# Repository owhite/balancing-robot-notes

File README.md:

# Balancing Robot Design and Implementation

This repository is a structured set of lab notes and implementation records for developing a two-wheeled self-balancing robot. It documents the workflows from physical modeling and parameter measurement through firmware design, control implementation, and experimental validation.

The focus is on reproducibility and engineering rigor: measured motor parameters, deterministic control-loop behavior, system identification, control design tradeoffs, and verification testing are all captured alongside working code and experiments.

Topics covered include:
- Control design and validation workflows for balancing robots
- Motor parameter measurement (phase resistance, d/q inductance, damping)
- Deterministic embedded firmware structure for real-time control
- Encoder integration and signal integrity checks
- CAN communication and timing behavior
- Failure modes and debugging notes
- Practical test methods and instrumentation results

These notes are intended to make the development and validation process transparent and repeatable, not just to present final code.

## My balancing robot journey, specs and testing

* A subset of steps required to get a robot to stand [[LINK](DOCS/balancing_checklist.md)]
* Common issues that can break balancing in the brain board project [[LINK](DOCS/balancing_failures.md)]
* Firmware design choices that keep the balancing control loop deterministic [[LINK](DOCS/determinism_design.md)]
* Measuring phase resistance, d-axis, and q-axis inductance of a BLDC Motor [[LINK](DOCS/BLDC_inductance_measurement.md)]
* Prompt ChatGPT so it is less of a exhuberant cheerleader and more of a skeptical lab partner: [[LINK](DOCS/chatGPT_tips.md)]
* Development of the robot control board [[LINK](brainboardV1.2/README.md)]

## Not totally coherent discussions:
* [LQR](DOCS/learn_LQR.md). 
* Using the MT6701 [[LINK](DOCS/MT6701.md)] → works great but required some minor modifications to MESC position and [velocity measurement](DOCS/pos_vel_CAN.md)
* Measuring jitter on the MESC [[LINK](DOCS/jitter_testing.md)] → none found at current operating speeds
* Implementing CAN [[LINK](DOCS/CAN.md)]
* Notes about MESC [[LINK](DOCS/MESC_control_variables.md)]
* The inadequacies of [PID](DOCS/PID_position.md). 
* How the brain board firmware works: [teensy code](DOCS/teensy_firmware_walkthrough.md). 
* Brain board firmware [[LINK](DOCS/software_specs.md)]

## Laboratory notes, 2025

* [Position hold](DOCS/sept12_position_hold.md)
* [Controller issues](DOCS/sept18_controller_issues.md)
* [Torque nonlinearity](DOCS/sept19_torque_nonlinearity.md)
* [PID notes](DOCS/sept23_PID_notes.md)
* [Least squares](DOCS/sept30_least_squares.md)
* [Torque response](DOCS/oct03_torque_response.md)
* [LQR modeling](DOCS/oct11_LQR_modeling.md)
* [LQR height](DOCS/oct12_LQR_height.md)
* [IMU testing](DOCS/nov16_IMU.md)

## Let's be real

**You probably will not want to hear this.** If you came here for the code to make a balancing robot, it is here, but it probably wont help. 

You might assume building a balancing robot is mostly a matter of assembling parts and flashing someone else’s code onto it. I used to think that too — until I finally worked out how to create on one. Balancing robots are not just bolted together -- they are tuned and integrated. Everything about them depends on tight interactions between hardware, sensors, motors, and feedback loops, and those interactions are different for every single robot.

A balancing robot is a dynamic control system, not a static device. It’s constantly trying to predict its own motion, measure its own tilt, compensate for delays, cancel vibration, and stabilize itself against gravity — hundreds of times per second. That means even small differences in hardware completely change the way the controller behaves. For example:

- Motors & ESCs: Different torque curves, different dead zones, different current limits, different FOC tuning.
- Wheels & tires: Diameter, traction, inertia, compliance — all change how the robot responds to torque.
- IMU: Sensitivity, noise, mounting vibration, sample timing, bias drift — all affect measured tilt.
- Microcontroller timing: Loop rate, jitter, scheduling delays, filter performance — all shift the controller behavior.
- Physical build: Height of the center of mass, frame stiffness, mass distribution — all change the robot’s dynamics.

If you change any of these, even slightly, the controller behaves differently. That’s why tuning is so time-consuming: you’re adjusting a control law to match the physics and imperfections of your specific robot.

_You are welcome to take my code and run it on your bot._ But unfortunately just like musical instruments or high-performance cars, balancing robots need to be customized, adjusted, and dialed in until the system “feels right.” The code is just the beginning; the tuning is the craft.

Why? Well:
- Your robot will not balance without a lot of tuning.
- What's most important to use this project as a prompt for making your own system
- Tuning is the real work — not a flaw, but part of the fun
- What really makes a robot stand is eliminating all the problems like jitter, timing issues, CAN communications, and modeling
- The code, and any intellectual ideas found here should remain in the public domain

**Finally, dearest reader**... I care about you, youre adorable, but quite unfortunately one of the ESCs that I use is closed source. Nothing would delight me more to make it open and I will try. Also note that for a while, I was using the Flipsky Mini FSESC6.7 pro 70A but I got tired of blowing them up because of cheap parts. Maybe some day I will make a version that runs on [moteus](https://mjbots.com/products/moteus-r4-11) or [odrive](https://odriverobotics.com) but right now that is not a priority. 

## The really great news is there is a new source of help. 

I want to be transparent about this: building a robot is not about writing code. I've written code for 20 plus years, in my case I worked through the entire project with ChatGPT as a kind of engineering partner. ChatG helps with asking questions, testing ideas, refining approaches, debugging weird behavior, and iterating the design over and over.

A balancing robot is a complex closed-loop control problem. As far as I know I never would have been able to use Google to address how robots behaves. ChatGPT creates the ability to explore those problems conversationally:

- When I wasn’t sure whether the IMU filtering was right, I asked it to analyze my data.
- It is incredible at helping with plotting results
- When I had motor vibration I couldn’t explain, I used chat to brainstorm possible causes and experiments.
- It taught me everything about LQR, interpretted equations, supplied python code to perform most of the calculations. It involved a lot of debugging -- when the LQR gains seemed wrong, I walked through the math with it.
- When the ESC behavior looked inconsistent, we debugged line by line until we understood it.
- When I needed to test an assumption, it helped me design the test.
- When something behaved strangely, I could describe it and get three possible hypotheses to try.

The project was far less like copying code from the internet and more like having a very patient senior engineer building one-off code bundles to eventually get this thing to stand. 

**We live in a world of prompt-driven engineering:** I shaped my thinking through prompts, refined those prompts based on the robot’s behavior, and used those conversations to build understanding that would have taken weeks on my own. ChatGPT didn’t “solve the problem” — it helped me reason through it, step by step.

So if you see this robot standing and balancing in a video, know that behind the scenes was not just hardware and code — it was hundreds of micro-conversations, experiments, adjustments, and iterations. ChatGPT was the scaffolding that helped me structure that process.

## ACKNOWLEDGEMENTS
This project would be completely impossible without the help, support and guidance of David Molony, developer of [MESC firmware](https://github.com/davidmolony/MESC_Firmware.git). Use of the MESC firmware is described throughout this repo.

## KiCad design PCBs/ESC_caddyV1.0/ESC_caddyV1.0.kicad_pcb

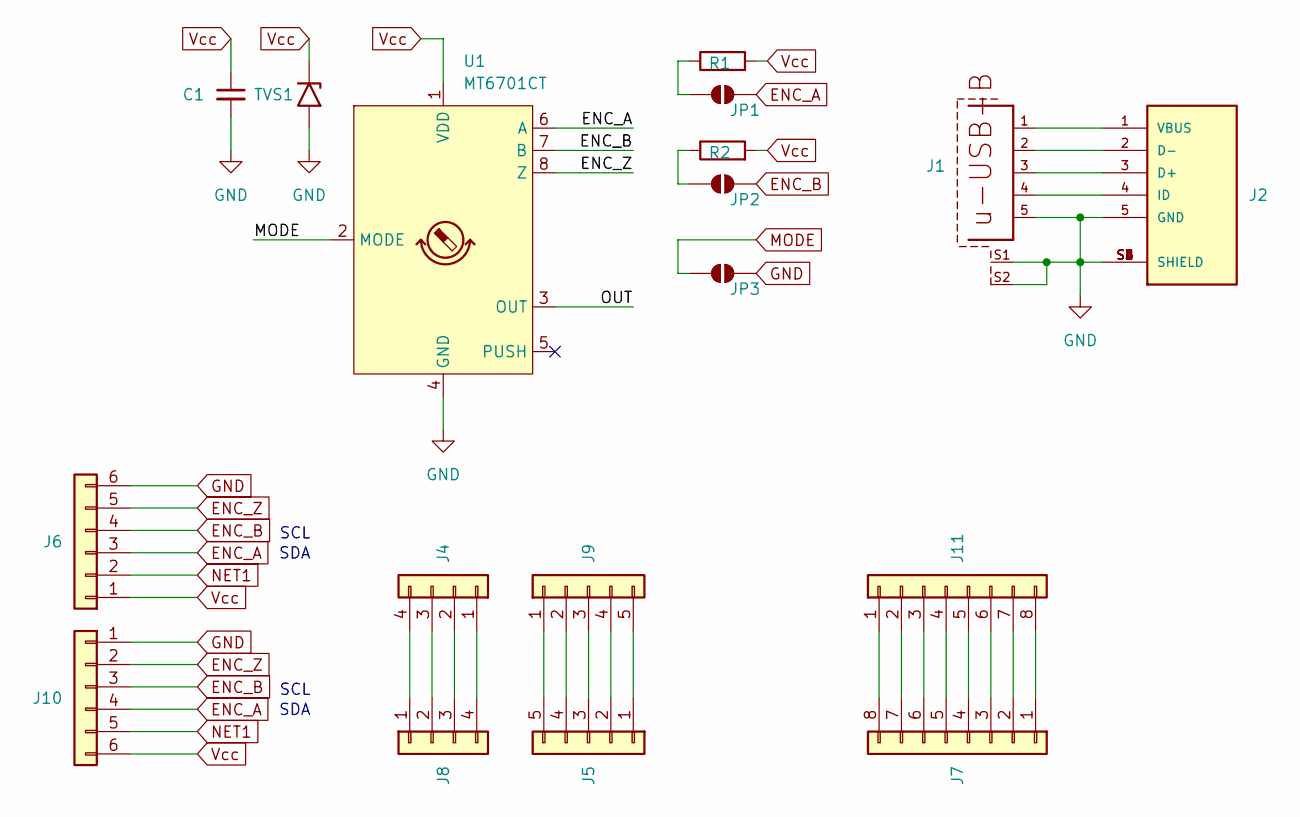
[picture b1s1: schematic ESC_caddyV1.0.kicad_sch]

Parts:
C1: C_Small; C_0603_1608Metric
J1: USB3145-30-1-A; FARNELL 2311903
J2: USB3150-30-130-A; GCT_USB3150-30-130-A; PARTREV A2
J4, J8: Conn_01x04; JST_PH_B4B-PH-K_1x04_P2.00mm_Vertical
J5, J9: Conn_01x05; JST_PH_B5B-PH-K_1x05_P2.00mm_Vertical
J6, J10: Conn_01x06; JST_PH_B6B-PH-K_1x06_P2.00mm_Vertical
J7, J11: Conn_01x08; JST_PH_B8B-PH-K_1x08_P2.00mm_Vertical
JP1, JP2, JP3: SolderJumper_2_Open; SolderJumper-2_P1.3mm_Open_RoundedPad1.0x1.5mm
R1, R2: R; R_0603_1608Metric
TVS1: SMFJ6.0A / SMFJ6.0CA; C_0805_2012Metric
U1: MT6701CT; SO-8_3.9x4.9mm_P1.27mm

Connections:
/OUT: U1.3 (OUT)
ENC_A: J6.3, J10.4, JP1.2 (B), U1.6 (A)
ENC_B: J6.4, J10.3, JP2.2 (B), U1.7 (B)
ENC_Z: J6.5, J10.2, U1.8 (Z)
GND: C1.2, J1.5, J1.S1, J1.S2, J2.5 (GND), J2.S1 (SHIELD), J2.S2 (SHIELD), J2.S3 (SHIELD), J2.S4 (SHIELD), J2.S5 (SHIELD), J2.S6 (SHIELD), J6.6, J10.1, JP3.2 (B), TVS1.2 (A2), U1.4 (GND)
MODE: JP3.1 (A), U1.2 (MODE)
NET1: J6.2, J10.5
unnamed: J1.3, J2.3 (D+)
unnamed: J1.2, J2.2 (D-)
unnamed: J1.4, J2.4 (ID)
unnamed: J1.1, J2.1 (VBUS)
unnamed: J4.1, J8.4
unnamed: J4.2, J8.3
unnamed: J4.3, J8.2
unnamed: J4.4, J8.1
unnamed: J5.1, J9.5
unnamed: J5.2, J9.4
unnamed: J5.3, J9.3
unnamed: J5.4, J9.2
unnamed: J5.5, J9.1
unnamed: J7.8, J11.1
unnamed: J7.7, J11.2
unnamed: J7.6, J11.3
unnamed: J7.5, J11.4
unnamed: J7.4, J11.5
unnamed: J7.3, J11.6
unnamed: J7.2, J11.7
unnamed: J7.1, J11.8
unnamed: JP1.1 (A), R1.1
unnamed: JP2.1 (A), R2.1
Vcc: C1.1, J6.1, J10.6, R1.2, R2.2, TVS1.1 (A1), U1.1 (VDD)

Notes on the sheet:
SCL
SDA

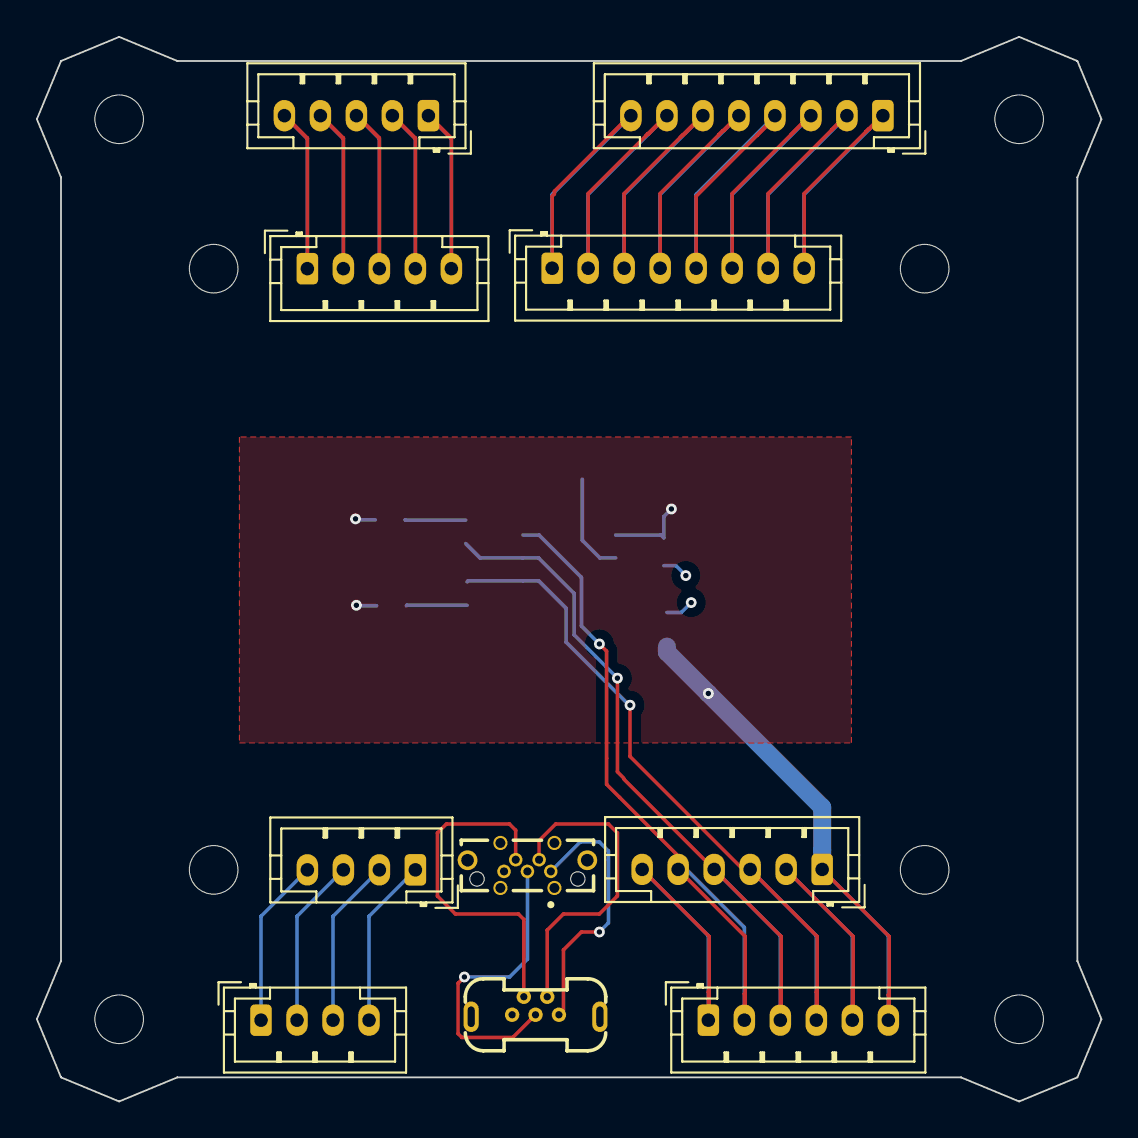
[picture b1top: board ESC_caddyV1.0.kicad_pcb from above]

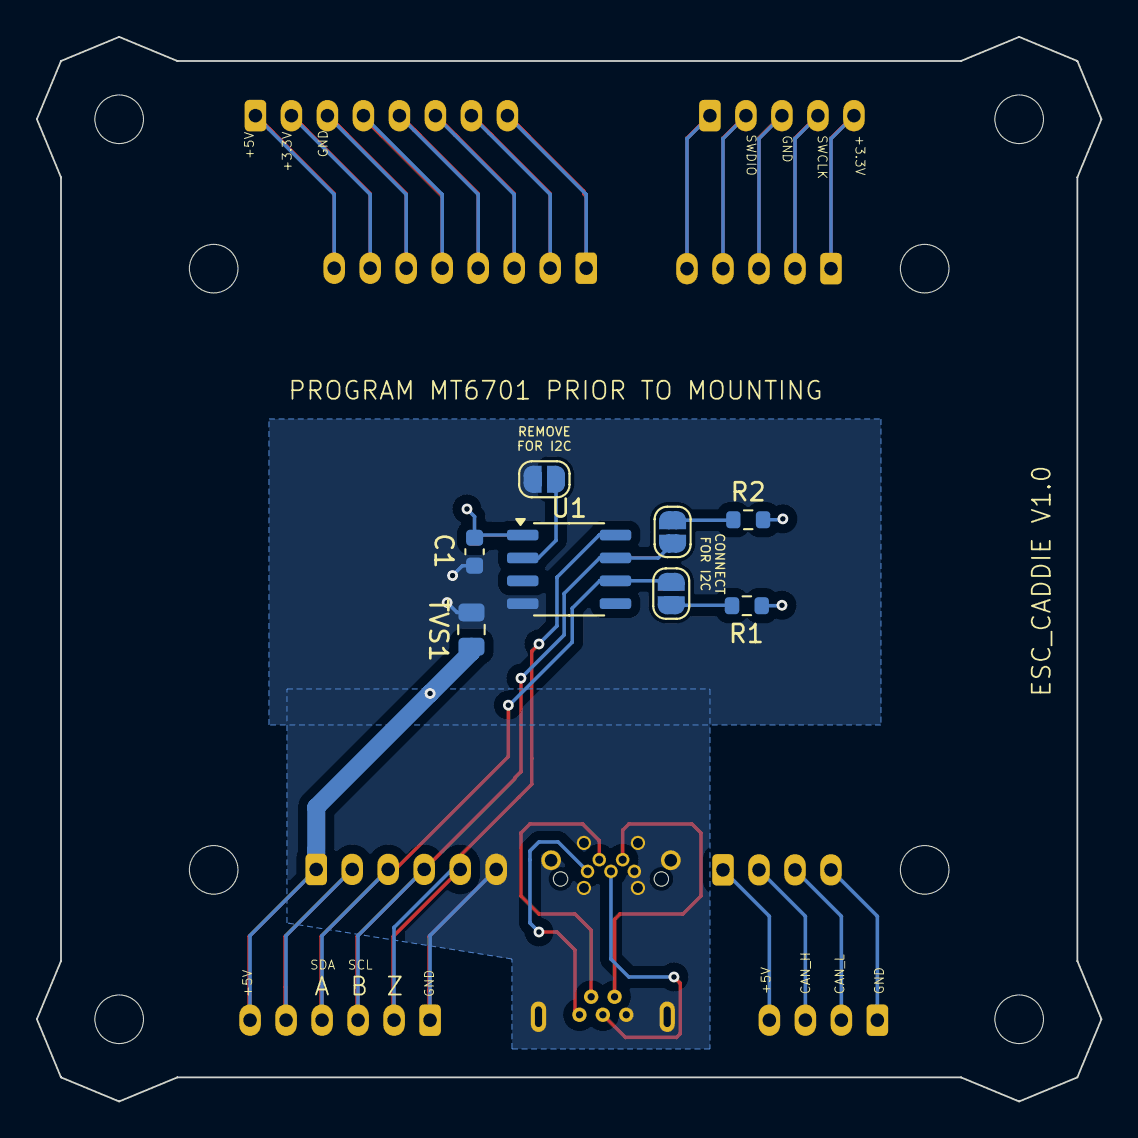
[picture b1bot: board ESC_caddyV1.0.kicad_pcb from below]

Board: 2 copper layers, 59.1 x 59.1 mm, 18 parts (8 on the bottom side), 30 nets.

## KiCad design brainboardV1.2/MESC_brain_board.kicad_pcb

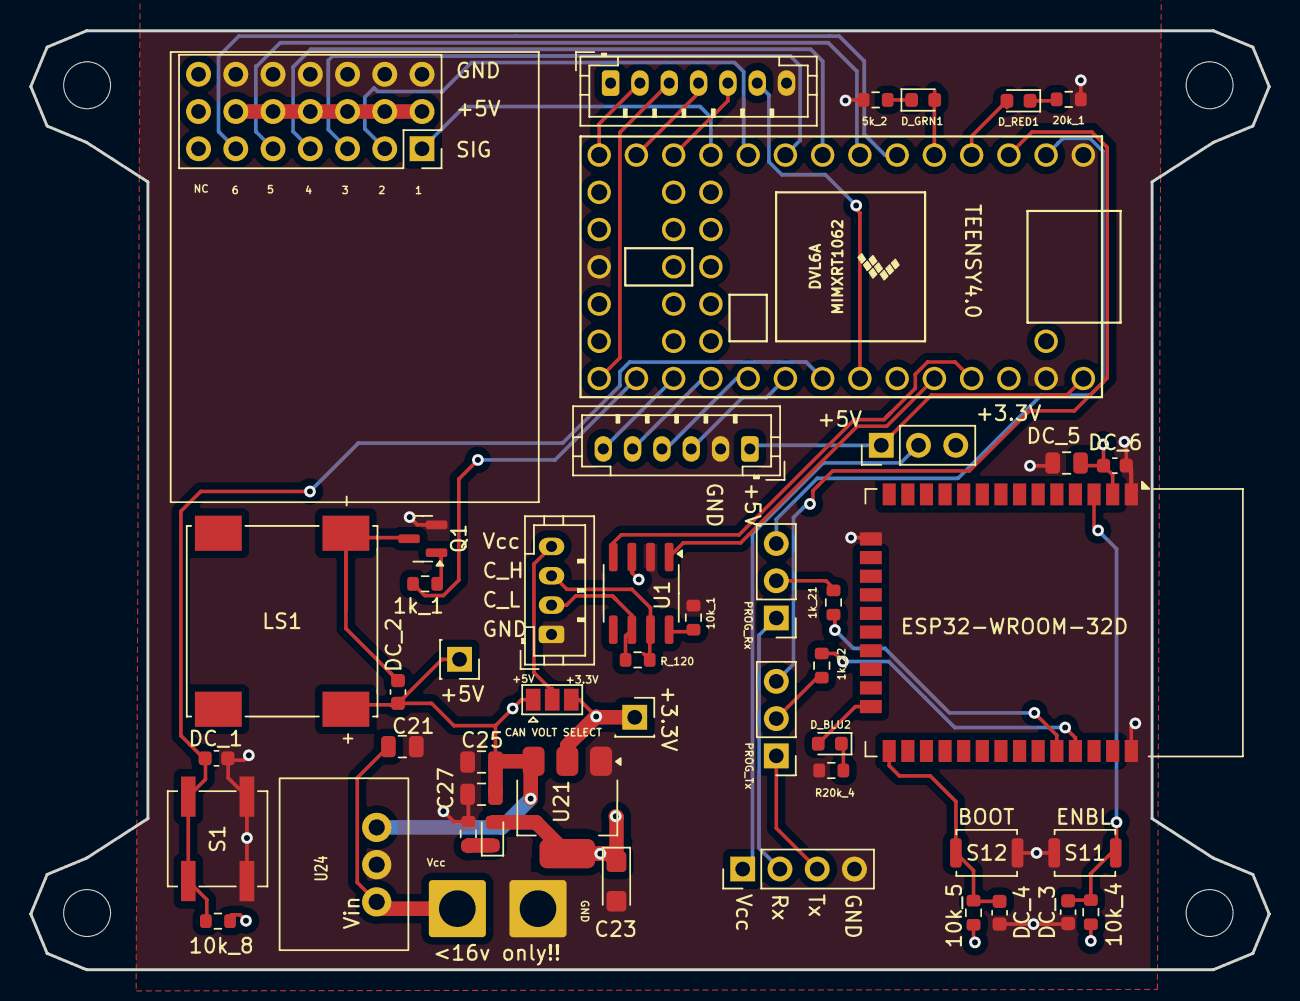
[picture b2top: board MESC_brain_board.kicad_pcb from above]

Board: 4 copper layers, 84.5 x 64.0 mm, 49 parts (0 on the bottom side), 47 nets.

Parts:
1k_1, 10k_1, 10k_4, 10k_5, 10k_8: 10k; R_0603_1608Metric
1k_21, 1k_22: 1k; R_0603_1608Metric
5k_2: 5k; R_0603_1608Metric
20k_1, 20k_21: 20k; R_0603_1608Metric
C21: 100nF; C_0805_2012Metric
C23: C_Polarized_Small_US; CP_EIA-3216-18_Kemet-A
C25, C27: 10uF; C_0805_2012Metric
CAN1: Conn_01x04; JST_PH_B4B-PH-K_1x04_P2.00mm_Vertical
DC_1, DC_2, DC_3, DC_4, DC_6: 100nF; C_0603_1608Metric
DC_5: 10uF; C_0805_2012Metric
D_BLU2: BLUE; LED_0603_1608Metric
D_BLU21: LED BLU; LED_0603_1608Metric
D_GRN1: LED GRN; LED_0603_1608Metric
D_RED1: LED RED; LED_0603_1608Metric
J1: Conn_01x18; my_PinSocket_3x07_P2.54mm_Vertical
J12, J13, J15: Conn_01x03; PinHeader_1x03_P2.54mm_Vertical
J14: SERIAL1; PinHeader_1x04_P2.54mm_Vertical
J21: Conn_01x07; JST_PH_B7B-PH-K_1x07_P2.00mm_Vertical
J22, J23: Conn_01x01; PinSocket_1x01_P2.54mm_Vertical
J24, J25: Conn_01x01; SolderWire-2sqmm_1x01_D2mm_OD3.9mm
JP1: SolderJumper_3_Open; SolderJumper-3_P1.3mm_Open_Pad1.0x1.5mm
LS1: Speaker; SPKR_CDS-13138-SMT-TR
MESC1: Conn_01x06; JST_PH_B6B-PH-K_1x06_P2.00mm_Vertical
Q1: my_BC337; SOT-23
R20k_4: 20k; R_0603_1608Metric
R_120: 120; R_0603_1608Metric
S1: TL3342F160QG; SW_SPST_B3SL-1022P
S11, S12: TL3342F160QG; SW_Push_SPST_NO_Alps_SKRK
U1: TJA1050T/CM,118; SOIC-8_3.9x4.9mm_P1.27mm
U2: Teensy4.0; Teensy40
U11: ESP32-WROOM-32D
U21: LD1117S18TR_SOT223; SOT-223-3_TabPin2
U24: 12_DCDC_5

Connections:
+3.3V: 10k_4.2, 10k_5.2, 10k_8.2, C23.1, DC_5.2, DC_6.1, D_BLU21.2 (A), J15.3, J21.1, J22.1, JP1.3 (B), U1.3 (VCC), U11.2 (VDD), U21.2 (VO)
+5V: C25.1, C27.1, DC_2.1, J1.2, J1.5, J1.8, J1.11, J1.14, J1.17, J15.1, J23.1, JP1.1 (A), LS1.1, MESC1.1, U2.33 (VIN), U21.3 (VI), U24.3 (VOUT)
/CAN_RX: U1.4 (R), U2.30 (23_A9_CRX1_MCLK1)
/CAN_TX: U1.1 (D), U2.29 (22_A8_CTX1)
BUTTON: 10k_8.1, DC_1.2, S1.2, U2.26 (19_A5_SCL0)
CAN_HI: CAN1.3, R_120.2, U1.7 (CANH)
CAN_LO: CAN1.2, R_120.1, U1.6 (CANL)
CS: J21.5, U2.12 (10_CS_MQSR)
ESP_EN: 10k_4.1, DC_3.2, S11.2, U11.3 (EN)
ESP_RX: J12.3, U2.2 (0_RX1_CRX2_CS1)
ESP_RX_OUT: J12.1, J14.2
ESP_TX: J13.3, U2.3 (1_TX1_CTX2_MISO1)
ESP_TX_OUT: J13.1, J14.3
GND: 5k_2.1, 10k_1.2, 20k_1.1, 20k_21.1, C21.2, C23.2, C25.2, C27.2, CAN1.1, DC_1.1, DC_3.1, DC_4.1, DC_5.1, DC_6.2, J1.3, J1.6, J1.9, J1.12, J1.15, J1.18, J14.4, J21.7, J24.1, MESC1.2, Q1.2 (E), R20k_4.1, S1.1, S11.1, S12.1, U1.2 (GND), U2.1 (GND), U2.17 (GND), U2.32 (GND), U11.1 (GND), U11.15 (GND), U11.38 (GND), U21.1 (GND), U24.2 (GND)
GPIO1: MESC1.3, U2.25 (18_A4_SDA0)
GPIO2: MESC1.4, U2.24 (17_A3_TX4_SDA1)
GPIO3: MESC1.5, U2.23 (16_A2_RX4_SCL1)
GPIO4: MESC1.6, U2.22 (15_A1_RX3_SPDIF_IN)
INT1: J21.6, U2.27 (20_A6_TX5_LRCLK1)
IO0: 10k_5.1, DC_4.2, S12.2, U11.25 (IO0)
LED1: D_RED1.2 (A), U2.4 (2_OUT2)
LED2: D_GRN1.2 (A), U2.5 (3_LRCLK2)
MISO: J21.2, U2.14 (12_MISO_MQSL)
MOSI: J21.4, U2.13 (11_MOSI_CTX1)
unnamed: CAN1.4, JP1.2 (C)
unnamed: D_BLU2.2 (A), U11.24 (IO2)
unnamed: D_BLU2.1 (K), R20k_4.2
unnamed: 20k_21.2, D_BLU21.1 (K)
unnamed: 5k_2.2, D_GRN1.1 (K)
unnamed: 20k_1.2, D_RED1.1 (K)
unnamed: 1k_21.2, J12.2
unnamed: 1k_22.2, J13.2
unnamed: J14.1, J15.2
unnamed: 1k_1.1, Q1.1 (B)
unnamed: DC_2.2, LS1.2, Q1.3 (C)
unnamed: 10k_1.1, U1.8 (Rs)
RC_Mode: J1.7, U2.9 (7_RX2_OUT1A)
RC_Steering: J1.1, U2.11 (9_OUT1C)
RC_Throttle: J1.4, U2.10 (8_TX2_IN1)
RC_X: J1.10, U2.8 (6_OUT1D)
RC_Y: J1.13, U2.7 (5_IN2)
RC_Z: J1.16, U2.6 (4_BCLK2)
SCLK: J21.3, U2.20 (13_SCK_CRX1_LED)
SPEAKER: 1k_1.2, U2.21 (14_A0_TX3_SPDIF_OUT)
U0RXD: 1k_21.1, U11.34 (RXD0/IO3)
U0TXD: 1k_22.1, U11.35 (TXD0/IO1)
Vcc: C21.1, J25.1, U24.1 (VIN)

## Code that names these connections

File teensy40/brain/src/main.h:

#ifndef MAIN_H
#define MAIN_H

#include <Arduino.h>
#include <IntervalTimer.h>
#include <FlexCAN_T4.h>

// ================= Pins from your board =================
#define LED1_PIN        2
#define LED2_PIN        3
#define PUSHBUTTON_PIN  17
#define SPEAKER_PIN     13

// ================= RC PWM (4 channels) =================
#define RC_INPUT1       9
#define RC_INPUT2       8
#define RC_INPUT3       7
#define RC_INPUT4       6

#define CAN_TX          24
#define CAN_RX          25

#endif // MAIN_H

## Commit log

2025-08-31 changed some files
2025-08-31 doc changes
2025-08-31 added jitter documentation
2025-09-02 new CAN documentation
2025-09-03 fixed some CAN code
2025-09-03 fixed can code
2025-09-03 added docs
2025-09-04 added MESC_control_variables.md
2025-09-07 minor changes
2025-09-07 change to documentation
2025-09-08 edited documentation
2025-09-08 initialized MPU6050 code
2025-09-09 added lots of RC input stuff
2025-09-09 significant progress on controlLoop()
2025-09-10 added determinism document, and refactored code
2025-09-11 docs: add TODOs to determinism_design.md for Supervisor map, background tasks, telemetry philosophy, and cross-links
2025-09-11 additional touchups to loadTelemetryPacket()
2025-09-12 just fooling around
2025-09-12 starting to work on position-hold
2025-09-16 more docs
2025-09-16 changed docs
2025-09-18 created list of controller issues
2025-09-19 nightly build
2025-09-19 new can_terminal
2025-09-20 documenting PID issues
2025-09-21 finally got PID working. See PID_fail folder
2025-09-28 added modeling folder
2025-09-29 more modeling
2025-09-30 modeling
2025-09-30 added more documentation
2025-09-30 testing STLs
2025-09-30 modeling scripts
2025-10-02 prep for torque response
2025-10-03 finished first experiments raising pendulum
2025-10-10 nothing much
2025-10-10 created new STL->URDF generator
2025-10-11 oct11_LQR_modeling.md
2025-10-15 added inclusion of b_term into K-matrix calc
2025-10-19 LQR milestone complete
2025-10-20 working on LQI
2025-10-22 completed LQI position control of motor
2025-10-22 LQI documentation
2025-10-29 LQR modeling of balance bot
2025-11-05 working out IMU issues
2025-11-07 designed ESC caddy
2025-11-08 IMU testing
2025-11-10 started on brain board v1.2
2025-11-10 finalizing brain board v1.2
2025-11-12 documentation stuff
2025-11-14 working on ICM42688
2025-11-14 implemented ICM42688
2025-11-16 ICM42688 testing
2025-11-16 balance_TWR_mode checkpoint
2025-11-18 more TWR testing
2025-11-23 vibration reduction / filtering
2025-11-25 first time the bot stood up
2025-12-28 BLDC inductance measurement
2026-01-09 stuff
2026-01-12 created MT6701_12mm
2026-01-12 Rename motor_deets.3dm to motor_deets.md
2026-01-12 Fix formatting of motor details headings
2026-01-12 Remove redundant set parameters from motor details
2026-01-12 Format motor parameters in motor_deets.md
2026-01-12 Add QS165 V2 parameters to motor_deets.md
2026-01-15 added some documentation
2026-01-20 more wood robot design
2026-01-23 refactoring modeling directory
2026-01-23 working on modeling
2026-01-26 spin decay calculation
2026-01-28 worked on generate_TWR_data.py
2026-01-29 more documentation in /modeling
2026-01-30 worked on DOCs
